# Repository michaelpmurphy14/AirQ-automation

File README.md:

# AirQ automation
 using ESP32C3 chip to collect and analyze air quality data
# Background
Create a sensor platform that can provide air quality data in a self-contained manner while also having the option to interface with an application.
 
A MiCS524 sensor for CO and a BME680 sensor for VOC, eCO2, and Temp/Humidity will connect to a Seeed Studio XIAO nRF52840 board and will be powered by an internal battery. The board will transmit data to an integrated RGB led and audible alert module and will also push data over BLE and WiFi to an application server. The device will be addressable by a single momentary push-button switch for checking battery status, pairing, etc...
 
The device will be able to be charged through the usb-c port on the nRF52840 board, and battery life will be 5-7 days on a single charge under normal load. The device will connect to any MagSafe device and will be able to provide charge-through capabilities when plugged in, as well as the capability to act as a standalone back-up power-bank to the connected device for a limited period
# Hardware Setup
## Bill of Materials
[Seed XIAO ESP32C3](https://www.seeedstudio.com/Seeed-XIAO-ESP32C3-p-5431.html)

[MICS 5524 Sensor](https://wiki.dfrobot.com/Fermion__MEMS_Gas_Sensor___MiCS-5524_SKU_SEN0440)

[BME680 Sensor](https://www.adafruit.com/product/3660)

[Buzzer]

[RGB Led]

[Li-Po Battery]

[QI Wireless Charging Unit]

## Technical Challenges
### Calibration
Each device will have to manually calibrated to provide an accurate range of gas readings from the MIS5524 Sensor. To compare each sensor and chip configuration, we will use onboard tinyML to calibrate to known values and adjust for drift over time

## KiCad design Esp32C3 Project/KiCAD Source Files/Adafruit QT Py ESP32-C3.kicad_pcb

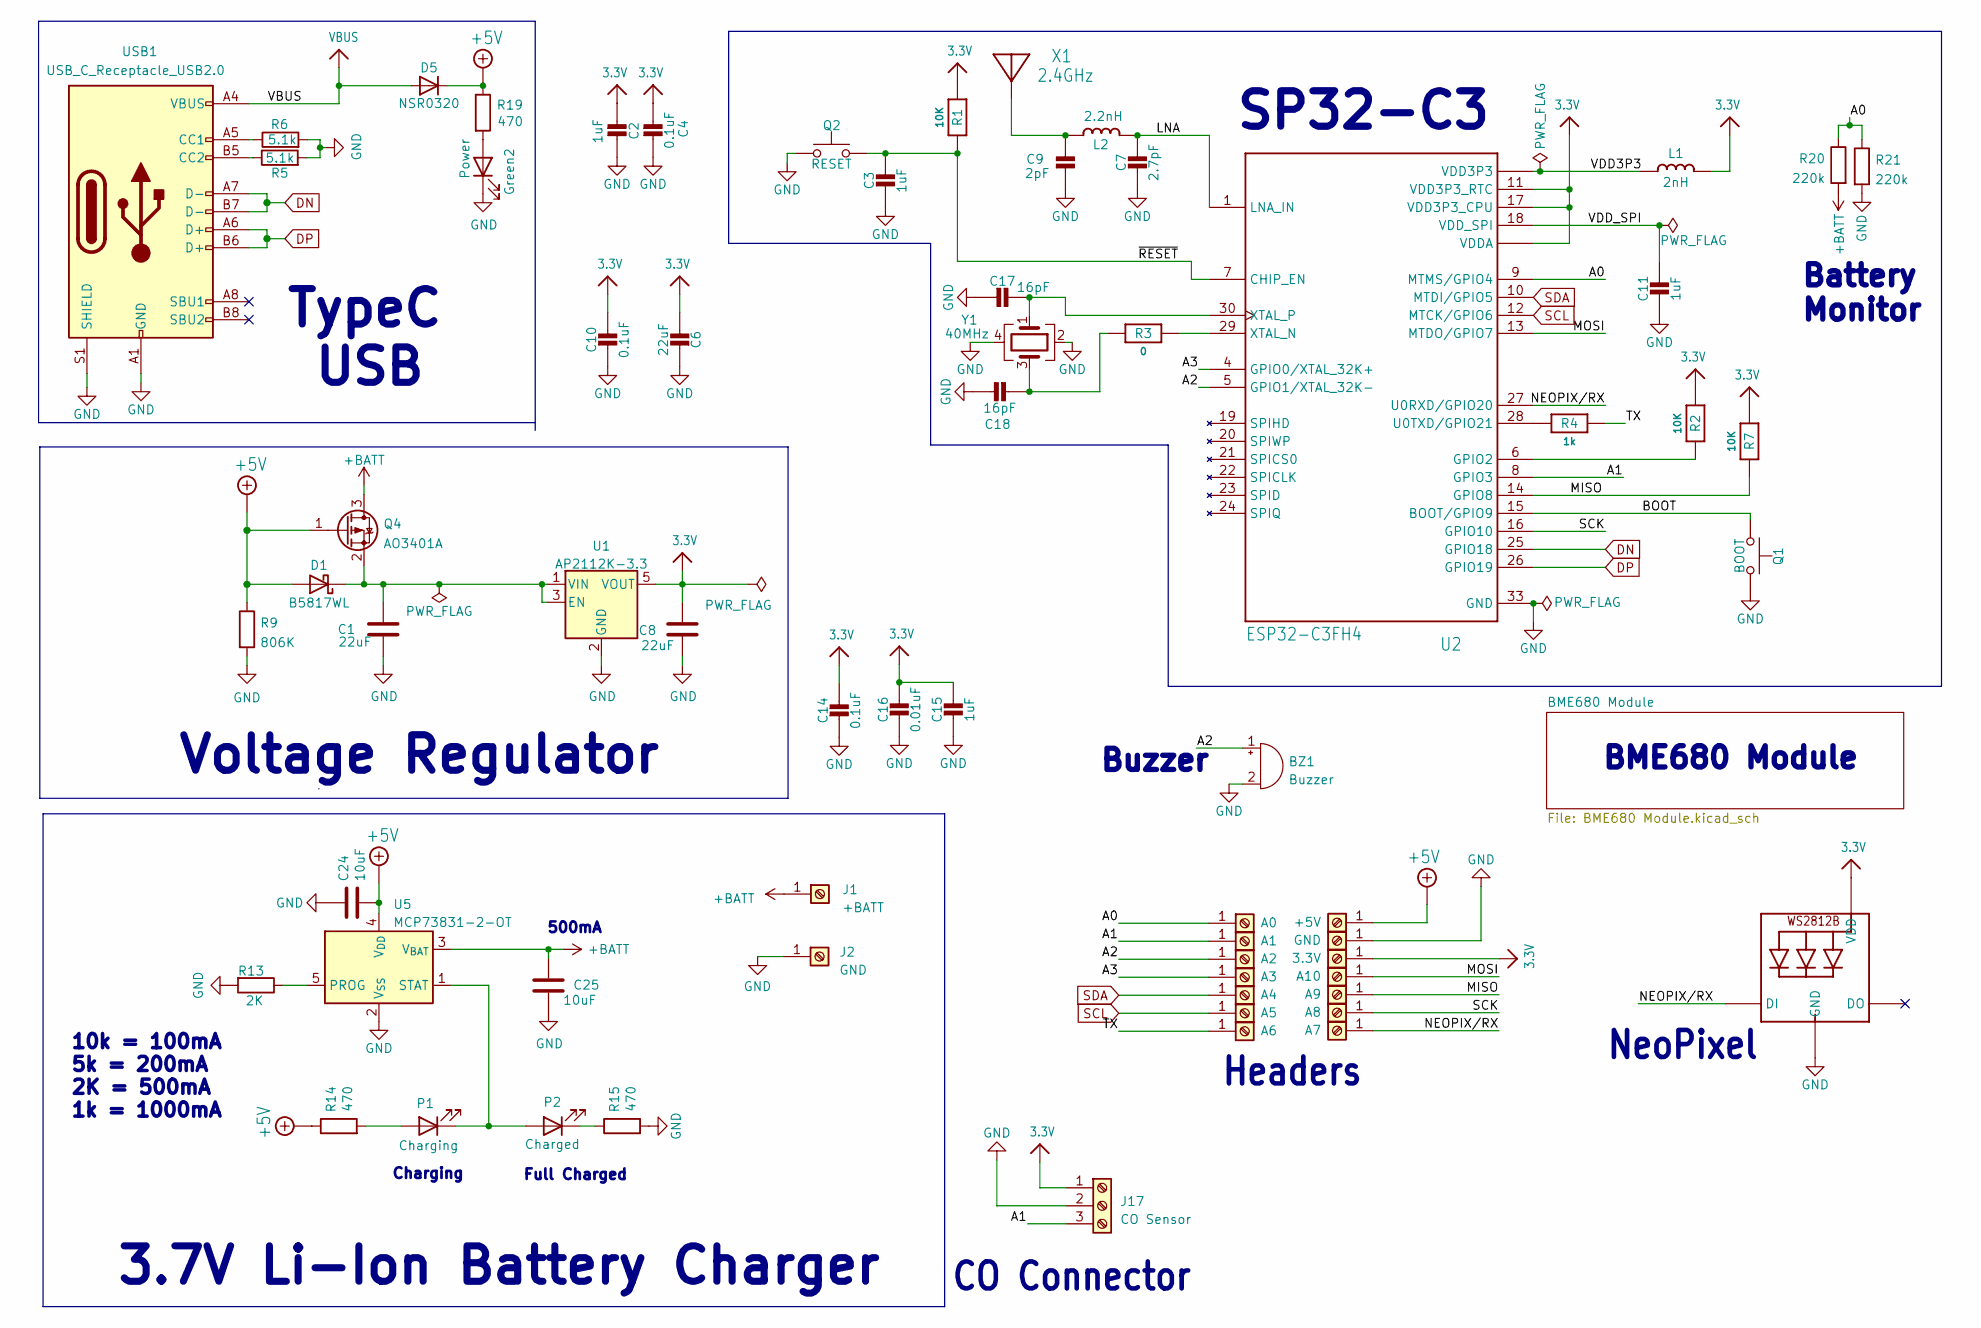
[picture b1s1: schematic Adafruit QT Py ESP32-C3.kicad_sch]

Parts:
BZ1: Buzzer; PinHeader_1x02_P2.54mm_Vertical
C1, C6, C8: 22uF; C_0805_2012Metric
C2, C3, C11, C15: 1uF; C_0402_1005Metric
C4, C10, C14: 0.1uF; C_0402_1005Metric
C7: 2.7pF; C_0402_1005Metric
C9: 2pF; C_0402_1005Metric
C16: 0.01uF; C_0402_1005Metric
C17, C18: 16pF; C_0402_1005Metric
C24: 10uF; C_0603_1608Metric
C25: 10uF; C_0603_1608Metric; LCSC C19702
D1: B5817WL; D_SOD-123F; LCSC C122853
D5: NSR0320; SOD-323_MINI; LCSC C48192
Green2: Power; LED_0603_1608Metric; LCSC C72041
J1: +BATT; 2x2_SMD_Conn
J2: GND; 2x2_SMD_Conn
J3: A0; 1X01_CASTEL
J4: A1; 1X01_CASTEL
J5: A2; 1X01_CASTEL
J6: A3; 1X01_CASTEL
J7: A4; 1X01_CASTEL
J8: A5; 1X01_CASTEL
J9: A6; 1X01_CASTEL
J10: +5V; 1X01_CASTEL
J11: GND; 1X01_CASTEL
J12: 3.3V; 1X01_CASTEL
J13: A10; 1X01_CASTEL
J14: A9; 1X01_CASTEL
J15: A8; 1X01_CASTEL
J16: A7; 1X01_CASTEL
J17: CO Sensor; PinHeader_1x03_P2.54mm_Vertical
L1: 2nH; L_0402_1005Metric
L2: 2.2nH; L_0402_1005Metric
LED1: WS2812B_SK6805_1515; SK6805_1515; LCSC C2890035
P1: Charging; LED_0603_1608Metric; LCSC C72041
P2: Charged; LED_0603_1608Metric; LCSC C72041
Q1: BOOT; SW-SMD-TS-1088-AR02016; LCSC C720477
Q2: RESET; SW-SMD-TS-1088-AR02016; LCSC C720477
Q4: AO3401A; SOT-23; LCSC C15127
R1, R2, R7: 10K; R_0402_1005Metric
R3: 0; R_0402_1005Metric
R4: 1k; R_0402_1005Metric
R5, R6: 5.1k; R_0402_1005Metric
R9: 806K; C_0603_1608Metric; LCSC C23250
R13: 2K; R_0603_1608Metric
R14, R15, R19: 470; R_0603_1608Metric
R20, R21: 220k; R_0402_1005Metric
U1: AP2112K-3.3; SOT-25-5_L3.0-W1.8-P0.95-LS3.0-BR
U2: ESP32-C3FH4; QFN32_5MM
U5: MCP73831-2-OT; SOT-23-5
USB1: USB_C_Receptacle_USB2.0; USB_C_Receptacle_HRO_TYPE-C-31-M-12
X1: 2.4GHz; ANT_2450AT18B100; LCSC C89334
Y1: 40MHz; Crystal_SMD_2016-4Pin_2.0x1.6mm; LCSC C501798

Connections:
+5V: C24.1, D1.2 (A), D5.C, J10.1, Q4.1 (G), R9.1, R14.1, R19.1, U5.4 (V_{DD})
+BATT: C25.1, J1.1, Q4.3 (D), R20.2, U5.3 (V_{BAT})
/A0: J3.1, R20.1, R21.1, U2.9 (MTMS/GPIO4)
/A1: J4.1, J17.3, U2.8 (GPIO3)
/A2: BZ1.1 (-), J5.1, U2.5 (GPIO1/XTAL_32K-)
/A3: J6.1, U2.4 (GPIO0/XTAL_32K+)
/BOOT: Q1.2, U2.15 (BOOT/GPIO9)
/LNA: C7.1, L2.1, U2.1 (LNA_IN)
/MISO: J14.1, R7.2, U2.14 (GPIO8)
/MOSI: J13.1, U2.13 (MTDO/GPIO7)
/NEOPIX/RX: J16.1, LED1.1 (DI), U2.27 (U0RXD/GPIO20)
/SCK: J15.1, U2.16 (GPIO10)
/TX: J9.1, R4.2
/VDD3P3: L1.2, U2.2 (VDD3P3), U2.3 (VDD3P3)
/VDD_SPI: C11.1, U2.18 (VDD_SPI)
/~RESET: C3.1, Q2.1, R1.2, U2.7 (CHIP_EN)
DN: U2.25 (GPIO18), USB1.A7 (D-), USB1.B7 (D-)
DP: U2.26 (GPIO19), USB1.A6 (D+), USB1.B6 (D+)
unnamed: C18.1, R3.1, Y1.3
unnamed: C1.1, D1.1 (K), Q4.2 (S), U1.1 (VIN), U1.3 (EN)
unnamed: Green2.2 (A), R19.2
unnamed: P1.2 (A), R14.2
unnamed: P1.1 (K), P2.2 (A), U5.1 (STAT)
unnamed: P2.1 (K), R15.1
unnamed: R2.2, U2.6 (GPIO2)
unnamed: R4.1, U2.28 (U0TXD/GPIO21)
unnamed: R3.2, U2.29 (XTAL_N)
unnamed: C17.1, U2.30 (XTAL_P), Y1.1
unnamed: R13.1, U5.5 (PROG)
unnamed: R6.1, USB1.A5 (CC1)
unnamed: R5.1, USB1.B5 (CC2)
unnamed: C9.1, L2.2, X1.FP
SCL: J8.1, U2.12 (MTCK/GPIO6); also elsewhere on the board
SDA: J7.1, U2.10 (MTDI/GPIO5); also elsewhere on the board
VBUS: D5.A, USB1.A4 (VBUS), USB1.A9 (VBUS), USB1.B4 (VBUS), USB1.B9 (VBUS)

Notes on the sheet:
Headers
NeoPixel
CO Connector
Battery Monitor
Buzzer
10k = 100mA 5k = 200mA 2K = 500mA 1k = 1000mA
3.7V Li-Ion Battery Charger
TypeC
BME680 Module
500mA
Voltage Regulator
Charging
Full Charged
USB
SP32-C3

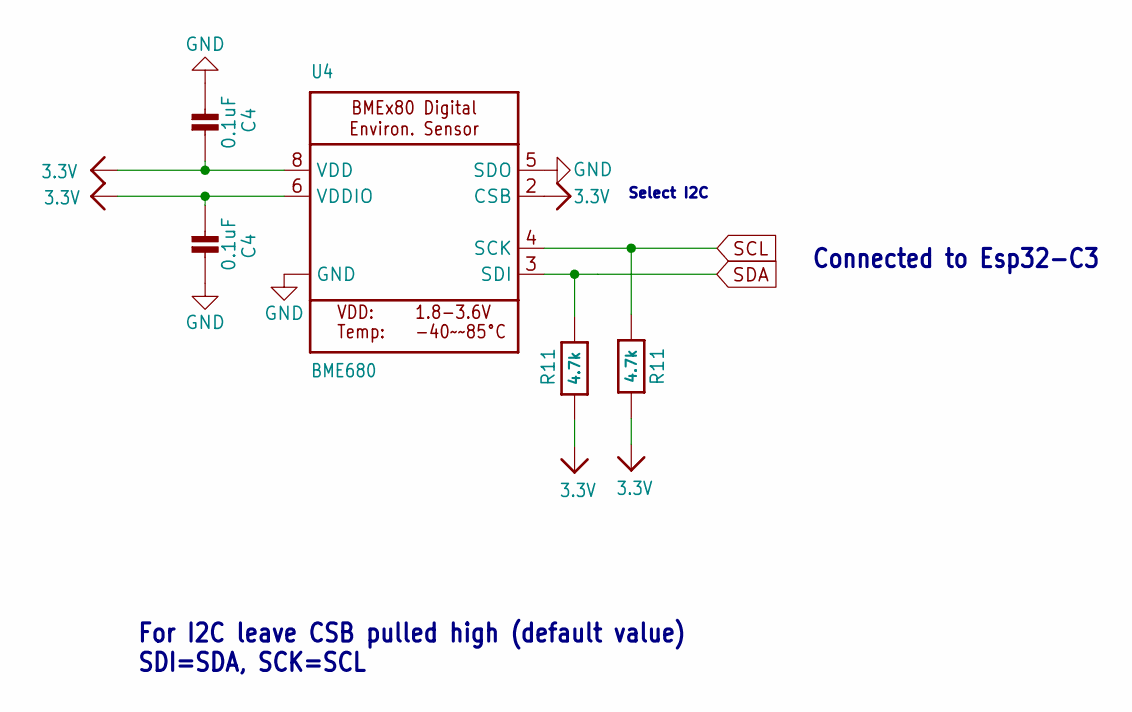
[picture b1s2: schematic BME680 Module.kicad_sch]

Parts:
C4: 0.1uF; C_0402_1005Metric
R11: 4.7k; R_0402_1005Metric
U4: BME680; BME680-LGA-8_L3.0-W3.0-P0.80-TR; LCSC C125972

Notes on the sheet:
Select I2C
Connected to Esp32-C3
For I2C leave CSB pulled high (default value) SDI=SDA, SCK=SCL

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
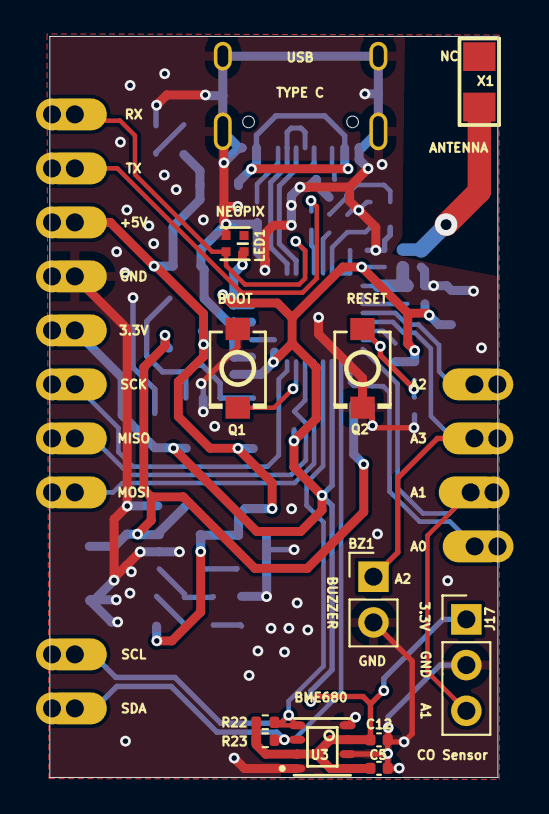
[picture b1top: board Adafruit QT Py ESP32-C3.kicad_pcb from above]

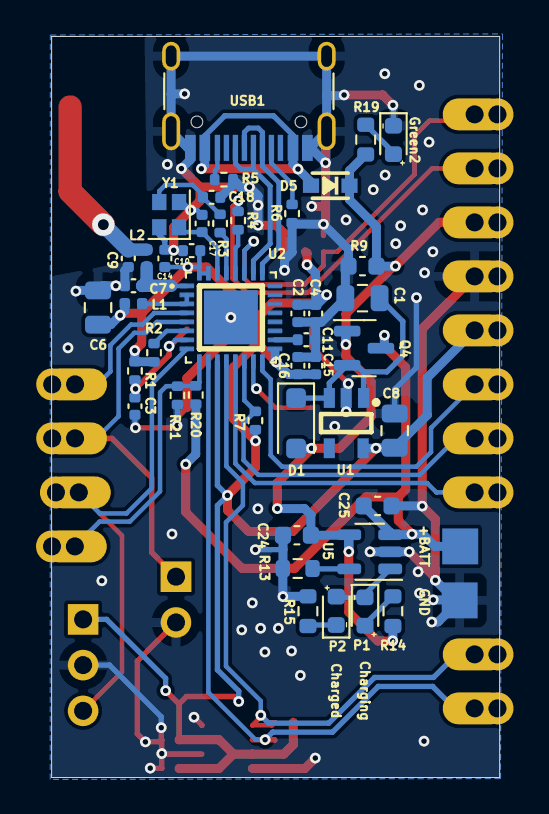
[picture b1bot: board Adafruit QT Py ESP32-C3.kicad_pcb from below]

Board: 2 copper layers, 24.9 x 41.2 mm, 71 parts (46 on the bottom side), 37 nets.

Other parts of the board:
C5, C12: 0.1uF; C_0402_1005Metric
R22, R23: 4.7k; R_0402_1005Metric
U3: BME680; BME680-LGA-8_L3.0-W3.0-P0.80-TR

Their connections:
SCL: R22.1, U3.4 (SCK); also elsewhere on the board
SDA: R23.1, U3.3 (SDI); also elsewhere on the board

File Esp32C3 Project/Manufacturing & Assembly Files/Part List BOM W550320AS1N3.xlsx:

Item | Qty | Reference(s) | Value | Footprint | LCSC Part# | Purchase Link
1 | 1 | BZ1 | Buzzer | Connector_PinHeader_2.54mm:PinHeader_1x02_P2.54mm_Vertical | C49661 | https://www.lcsc.com/product-detail/Female-Headers_BOOMELE-B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
2 | 2 | C1, C8 | 22uF | Ahsan Libs:C_0805_2012Metric | C45783 | https://www.lcsc.com/product-detail/Multilayer-Ceramic-Capac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
3 | 4 | C2, C3, C11, C15 | 1uF | Ahsan Libs:C_0402_1005Metric | C52923 | https://www.lcsc.com/product-detail/Multilayer-Ceramic-Capac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
4 | 5 | C4, C5, C10, C12, C14 | 0.1uF | Ahsan Libs:C_0402_1005Metric | C307331 | https://www.lcsc.com/product-detail/Multilayer-Ceramic-Capac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
5 | 1 | C6 | 22uF | Ahsan Libs:C_0805_2012Metric | C45783 | https://www.lcsc.com/product-detail/Multilayer-Ceramic-Capac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
6 | 1 | C7 | 2.7pF | Ahsan Libs:C_0402_1005Metric | C1561 | https://www.lcsc.com/product-detail/Multilayer-Ceramic-Capac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
7 | 1 | C9 | 2pF | Ahsan Libs:C_0402_1005Metric | C285089 | https://www.lcsc.com/product-detail/Multilayer-Ceramic-Capac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
8 | 1 | C16 | 0.01uF | Ahsan Libs:C_0402_1005Metric | C15195 | https://www.lcsc.com/product-detail/Multilayer-Ceramic-Capac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
9 | 2 | C17, C18 | 16pF | Ahsan Libs:C_0402_1005Metric | C161307 | https://www.lcsc.com/product-detail/Multilayer-Ceramic-Capac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
10 | 2 | C24, C25 | 10uF | Ahsan Libs:C_0603_1608Metric | C96446 | https://www.lcsc.com/product-detail/Multilayer-Ceramic-Capac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
11 | 1 | D1 | B5817WL | Diode_SMD:D_SOD-123F | C122853 | https://www.lcsc.com/product-detail/Schottky-Barrier-Diodes-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
12 | 1 | D5 | NSR0320 | Esp32-C3:SOD-323_MINI | C48192 | https://www.lcsc.com/product-detail/Schottky-Barrier-Diodes-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
13 | 1 | Green2 | Power | Ahsan Libs:LED_0603_1608Metric | C72041 | https://www.lcsc.com/product-detail/Light-Emitting-Diodes-LE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
14 | 1 | J17 | CO Sensor | Connector_PinHeader_2.54mm:PinHeader_1x03_P2.54mm_Vertical | C541850 | https://www.lcsc.com/product-detail/Female-Headers_XFCN-PM25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
15 | 1 | L1 | 2nH | Inductor_SMD:L_0402_1005Metric | C98758 | https://www.lcsc.com/product-detail/Inductors-SMD_TDK-MLG100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
16 | 1 | L2 | 2.2nH | Inductor_SMD:L_0402_1005Metric | C91240 | https://www.lcsc.com/product-detail/Inductors-SMD_Murata-Ele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
17 | 1 | LED1 | WS2812B_SK6805_1515 | Esp32-C3:SK6805_1515 | C2890035 | https://www.lcsc.com/product-detail/Light-Emitting-Diodes-LE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
18 | 1 | P1 | Charging | Ahsan Libs:LED_0603_1608Metric | C125094 | https://www.lcsc.com/product-detail/Light-Emitting-Diodes-LE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
19 | 1 | P2 | Charged | Ahsan Libs:LED_0603_1608Metric | C125099 | https://www.lcsc.com/product-detail/Light-Emitting-Diodes-LE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
20 | 1 | Q1 | BOOT | Ahsan Libs:SW-SMD-TS-1088-AR02016 | C720477 | https://www.lcsc.com/product-detail/Tactile-Switches_XUNPU-T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
21 | 1 | Q2 | RESET | Ahsan Libs:SW-SMD-TS-1088-AR02016 | C720477 | https://www.lcsc.com/product-detail/Tactile-Switches_XUNPU-T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
22 | 1 | Q4 | AO3401A | Package_TO_SOT_SMD:SOT-23 | C15127 | https://www.lcsc.com/product-detail/MOSFETs_Alpha-Omega-Semi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
23 | 2 | R1, R2 | 10K | Ahsan Libs:R_0402_1005Metric | C25744 | https://www.lcsc.com/product-detail/Chip-Resistor-Surface-Mo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
24 | 1 | R3 | 0 | Ahsan Libs:R_0402_1005Metric | C17168 | https://www.lcsc.com/product-detail/Chip-Resistor-Surface-Mo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
25 | 1 | R4 | 1k | Ahsan Libs:R_0402_1005Metric | C11702 | https://www.lcsc.com/product-detail/Chip-Resistor-Surface-Mo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
26 | 2 | R5, R6 | 5.1k | Ahsan Libs:R_0402_1005Metric | C25905 | https://www.lcsc.com/product-detail/Chip-Resistor-Surface-Mo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
27 | 1 | R7 | 10K | Ahsan Libs:R_0402_1005Metric | C25744 | https://www.lcsc.com/product-detail/Chip-Resistor-Surface-Mo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
28 | 1 | R9 | 806K | Ahsan Libs:C_0603_1608Metric | C23250 | https://www.lcsc.com/product-detail/Chip-Resistor-Surface-Mo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
29 | 1 | R13 | 2K | Ahsan Libs:R_0603_1608Metric | C22975 | https://www.lcsc.com/product-detail/Chip-Resistor-Surface-Mo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
30 | 3 | R14, R15, R19 | 470 | Ahsan Libs:R_0603_1608Metric | C23179 | https://www.lcsc.com/product-detail/Chip-Resistor-Surface-Mo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
31 | 2 | R20, R21 | 220k | Ahsan Libs:R_0402_1005Metric | C25767 | https://www.lcsc.com/product-detail/Chip-Resistor-Surface-Mo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
32 | 2 | R22, R23 | 4.7k | Ahsan Libs:R_0402_1005Metric | C25900 | https://www.lcsc.com/product-detail/Chip-Resistor-Surface-Mo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
33 | 1 | U1 | AP2112K-3.3 | Ahsan Libs:SOT-25-5_L3.0-W1.8-P0.95-LS3.0-BR | C51118 | https://www.lcsc.com/product-detail/Linear-Voltage-Regulator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
34 | 1 | U2 | ESP32-C3FH4 | Esp32-C3:QFN32_5MM | C2858491 | https://www.lcsc.com/product-detail/Microcontroller-Units-MC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
35 | 1 | U3 | BME680 | Ahsan Libs:BME680-LGA-8_L3.0-W3.0-P0.80-TR | C125972 | https://www.lcsc.com/product-detail/Temperature-and-Humidity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
36 | 1 | U5 | MCP73831-2-OT | Package_TO_SOT_SMD:SOT-23-5 | C424093 | https://www.lcsc.com/product-detail/Battery-Management-ICs_M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
37 | 1 | USB1 | USB_C_Receptacle_USB2.0 | Ahsan Libs:USB_C_Receptacle_HRO_TYPE-C-31-M-12 | C165948 | https://www.lcsc.com/product-detail/USB-Connectors_Korean-Hr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
38 | 1 | X1 | 2.4GHz | Esp32-C3:ANT_2450AT18B100 | C89334 | https://www.lcsc.com/product-detail/Antennas_Johanson-Dielec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
39 | 1 | Y1 | 40MHz | Crystal:Crystal_SMD_2016-4Pin_2.0x1.6mm | C501798 | https://www.lcsc.com/product-detail/Crystals_TST-TZ1269D_C50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

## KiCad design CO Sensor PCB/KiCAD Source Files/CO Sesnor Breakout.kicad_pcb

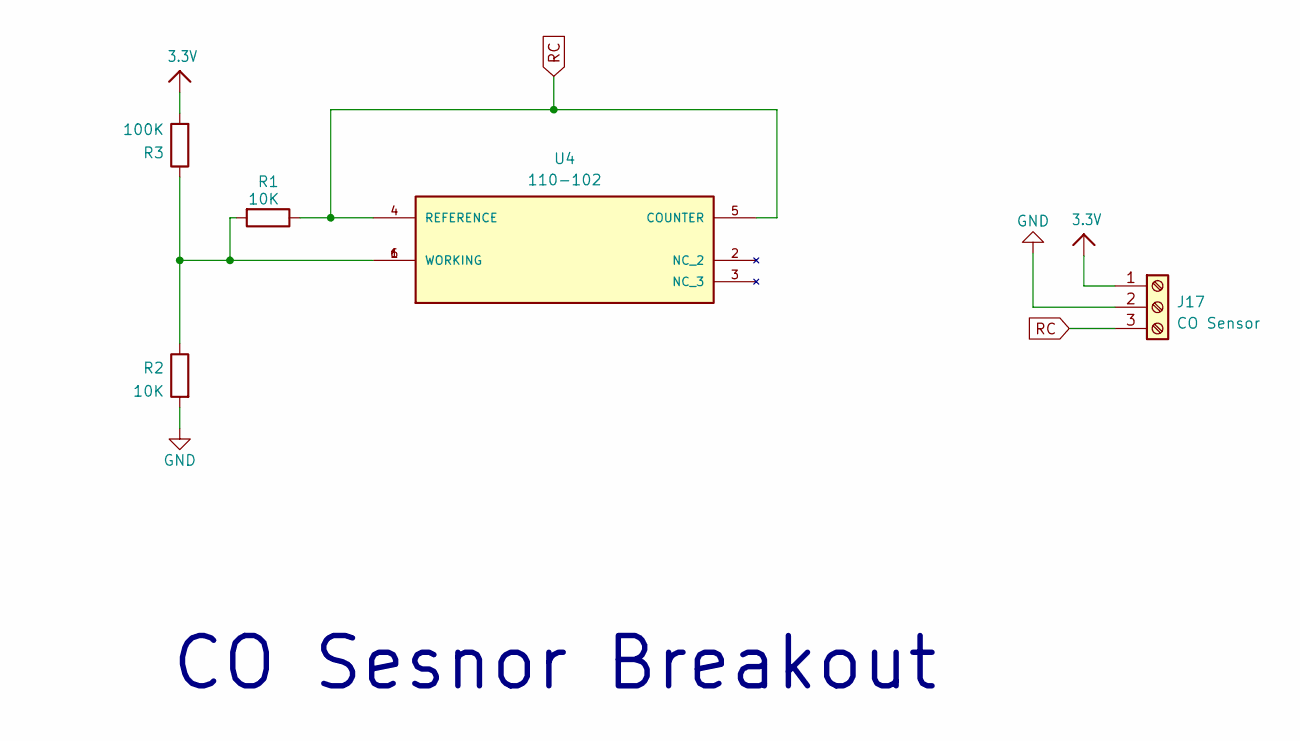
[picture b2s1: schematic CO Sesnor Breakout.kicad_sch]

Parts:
J17: CO Sensor; PinHeader_1x03_P2.54mm_Vertical
R1, R2: 10K; R_0805_2012Metric
R3: 100K; R_0805_2012Metric
U4: 110-102; CO Sensor; PARTREV April 2017

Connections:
3.3V: J17.1, R3.2
GND: J17.2, R2.2
unnamed: R1.2, R2.1, R3.1, U4.1 (WORKING), U4.6 (WORKING)
RC: J17.3, R1.1, U4.4 (REFERENCE), U4.5 (COUNTER)

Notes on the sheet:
CO Sesnor Breakout

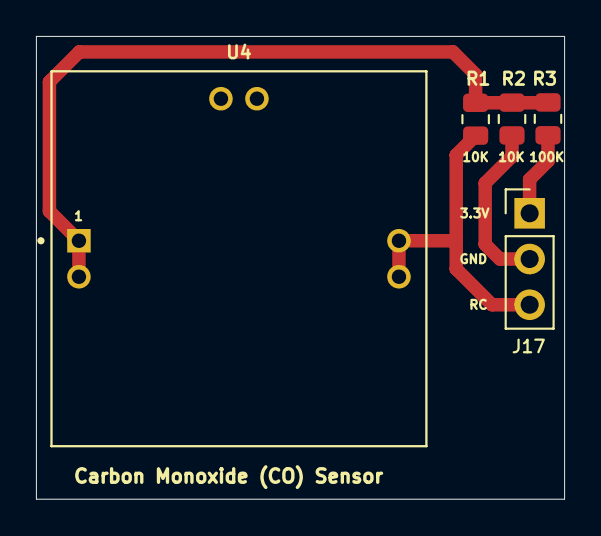
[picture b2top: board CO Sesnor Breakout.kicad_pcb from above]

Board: 2 copper layers, 29.3 x 25.7 mm, 5 parts (0 on the bottom side), 4 nets.

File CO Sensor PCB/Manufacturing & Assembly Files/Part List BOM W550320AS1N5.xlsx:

Item | Qty | Reference(s) | Value | Footprint | LCSC Part# | Purchase Link
1 | 1 | J17 | CO Sensor Conn | Connector_PinHeader_2.54mm:PinHeader_1x03_P2.54mm_Vertical | C2937625 | https://www.lcsc.com/product-detail/Pin-Headers_XFCN-PZ254V-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
2 | 2 | R1, R2 | 10K | Ahsan Libs:R_0805_2012Metric | C17414 | https://www.lcsc.com/product-detail/Chip-Resistor-Surface-Mo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
3 | 1 | R3 | 100K | Ahsan Libs:R_0805_2012Metric | C149504 | https://www.lcsc.com/product-detail/Chip-Resistor-Surface-Mo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
4 | 1 | U4 | 110-102 | Ahsan Libs:CO Sensor | Carbon Monoxide (CO) Sensor Current | https://www.digikey.com/en/products/detail/spec-sensors-llc/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

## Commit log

2023-11-21 Update index.html
    updated to include all BME680 sensor inputs and allows a buzzer to be controlled
2023-11-21 Update index.html
    added buzzer and battery percentage
2023-11-21 Update index.html
    trying to fix
2023-11-21 Update index.html
    LED fixes
2023-11-21 Create firmware
2023-11-21 Create web-app
2023-11-21 Rename index.html to web-app/index.html
2023-11-21 Rename app.js to web-app/app.js
2023-11-21 Update index.html
    bootstrap css
2023-11-21 VOC updates
2023-11-21 update for VOCs
2023-11-21 filter devices
2023-11-21 Combined bme680 characteristic
2023-11-21 Update app.js
    commented out buzzer
